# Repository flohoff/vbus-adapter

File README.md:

This repository contains a Vissmann VBUS Adapter KiCad 9 Project.

It uses a Wemos S2 Mini as the ESP32 Interface and offers a
CAN Bus for e.g. Vissmann Vitocal and a VBUS Interface for
connecting to a Vitrotrans a relabeled Resol.

It allows for connecting additional Sensors like DHT22 or DS1820

Currently the project is untested.

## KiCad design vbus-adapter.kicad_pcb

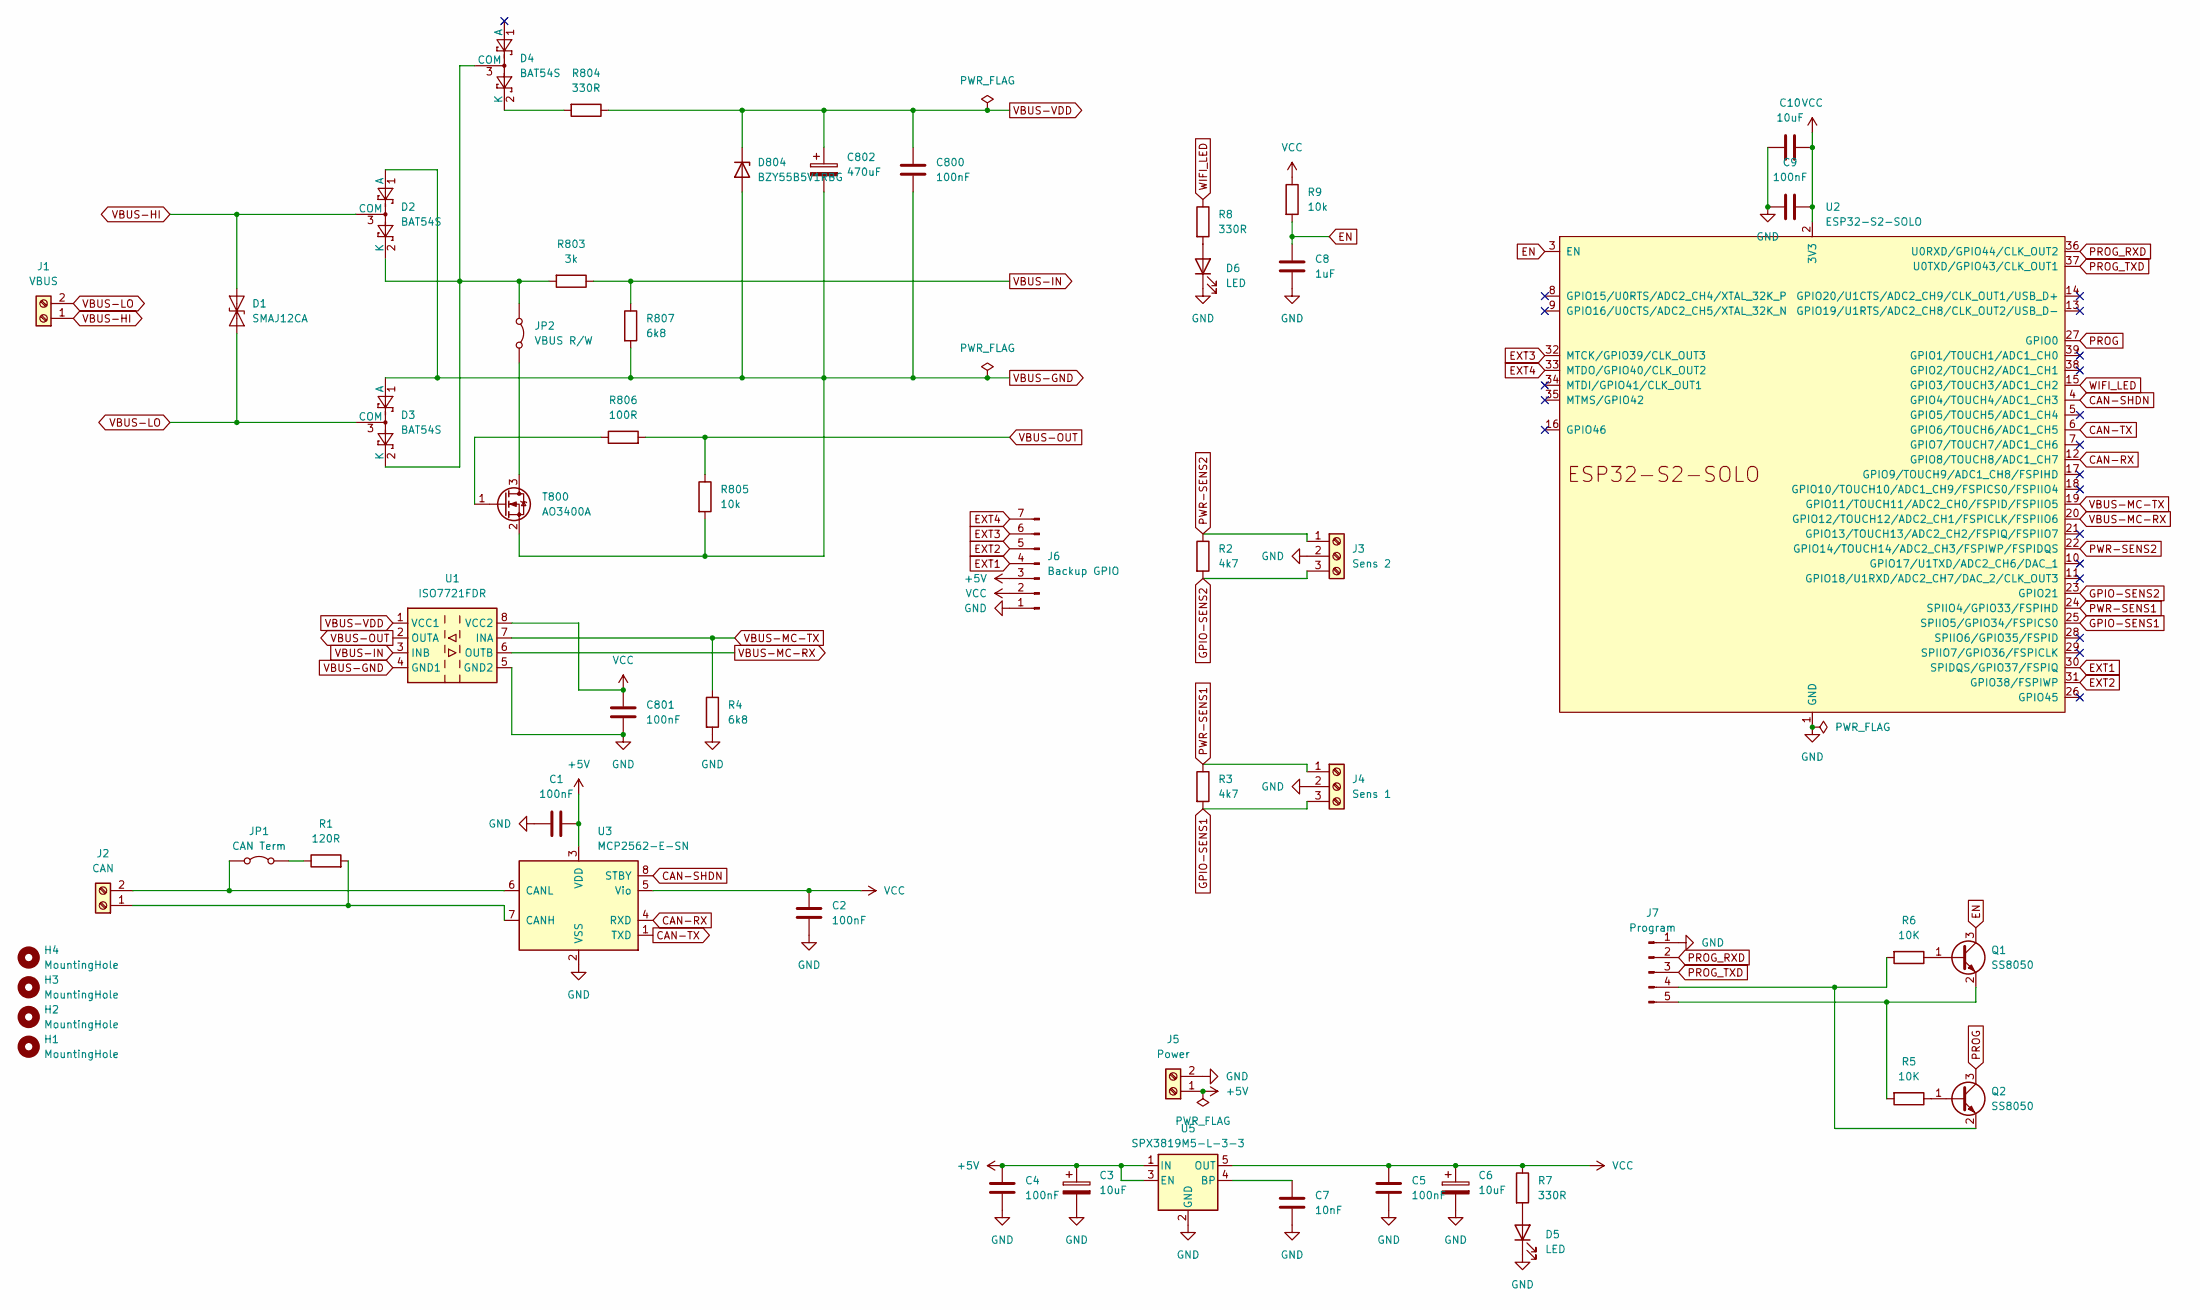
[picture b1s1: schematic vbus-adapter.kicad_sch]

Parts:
C1, C2, C4, C5, C800, C801: 100nF; C_0805_2012Metric_Pad1.18x1.45mm_HandSolder
C3, C6: 10uF; C_0805_2012Metric_Pad1.18x1.45mm_HandSolder
C7: 10nF; C_0805_2012Metric_Pad1.18x1.45mm_HandSolder
C8: 1uF; C_0805_2012Metric
C9: 100nF; C_0805_2012Metric
C10: 10uF; C_0805_2012Metric
C802: 470uF; CP_Elec_8x10
D1: SMAJ12CA; D_SMA
D2, D3, D4: BAT54S; SOT-23
D5, D6: LED; LED_0805_2012Metric_Pad1.15x1.40mm_HandSolder
D804: BZY55B5V1RBG; D_0805_2012Metric
H1, H2, H3, H4: MountingHole; MountingHole_3.2mm_M3_DIN965_Pad
J1: VBUS; TerminalBlock_Phoenix_MPT-0,5-2-2.54_1x02_P2.54mm_Horizontal
J2: CAN; TerminalBlock_Phoenix_MPT-0,5-2-2.54_1x02_P2.54mm_Horizontal
J3: Sens 2; TerminalBlock_Phoenix_MPT-0,5-3-2.54_1x03_P2.54mm_Horizontal
J4: Sens 1; TerminalBlock_Phoenix_MPT-0,5-3-2.54_1x03_P2.54mm_Horizontal
J5: Power; TerminalBlock_Phoenix_MPT-0,5-2-2.54_1x02_P2.54mm_Horizontal
J6: Backup GPIO; PinHeader_1x07_P2.54mm_Vertical
J7: Program; PinHeader_1x05_P2.54mm_Vertical
JP1: CAN Term; PinHeader_1x02_P2.54mm_Vertical
JP2: VBUS R/W; PinHeader_1x02_P2.54mm_Vertical
Q1, Q2: SS8050; SOT-23
R1: 120R; R_0805_2012Metric_Pad1.20x1.40mm_HandSolder
R2, R3: 4k7; R_0805_2012Metric_Pad1.20x1.40mm_HandSolder
R4, R807: 6k8; R_0805_2012Metric_Pad1.20x1.40mm_HandSolder
R5, R6: 10K; R_0805_2012Metric_Pad1.20x1.40mm_HandSolder
R7, R8, R804: 330R; R_0805_2012Metric_Pad1.20x1.40mm_HandSolder
R9: 10k; R_0805_2012Metric
R803: 3k; R_0805_2012Metric_Pad1.20x1.40mm_HandSolder
R805: 10k; R_0805_2012Metric_Pad1.20x1.40mm_HandSolder
R806: 100R; R_0805_2012Metric_Pad1.20x1.40mm_HandSolder
T800: AO3400A; SOT-23
U1: ISO7721FDR; SOIC-8_3.9x4.9mm_P1.27mm
U2: ESP32-S2-SOLO
U3: MCP2562-E-SN; SOIC-8_3.9x4.9mm_P1.27mm
U5: SPX3819M5-L-3-3; SOT-23-5

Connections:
+5V: C1.1, C3.1, C4.1, J5.1, J6.3, U3.3 (VDD), U5.1 (IN), U5.3 (EN)
CAN-RX: U2.12 (GPIO8/TOUCH8/ADC1_CH7), U3.4 (RXD)
CAN-SHDN: U2.4 (GPIO4/TOUCH4/ADC1_CH3), U3.8 (STBY)
CAN-TX: U2.6 (GPIO6/TOUCH6/ADC1_CH5), U3.1 (TXD)
EN: C8.1, Q1.3 (C), R9.2, U2.3 (EN)
EXT1: J6.4, U2.30 (SPIDQS/GPIO37/FSPIQ)
EXT2: J6.5, U2.31 (GPIO38/FSPIWP)
EXT3: J6.6, U2.32 (MTCK/GPIO39/CLK_OUT3)
EXT4: J6.7, U2.33 (MTDO/GPIO40/CLK_OUT2)
GND: C1.2, C2.2, C3.2, C4.2, C5.2, C6.2, C7.2, C8.2, C9.1, C10.1, C801.2, D5.1 (K), D6.1 (K), J3.2, J4.2, J5.2, J6.1, J7.1, R4.2, U1.5 (GND2), U2.1 (GND), U2.40 (GND), U2.41 (GND), U3.2 (VSS), U5.2 (GND)
GPIO-SENS1: J4.3, R3.2, U2.25 (SPIIO5/GPIO34/FSPICS0)
GPIO-SENS2: J3.3, R2.2, U2.23 (GPIO21)
unnamed: D2.2 (K), D3.2 (K), D4.3 (COM), JP2.1 (A), R803.2
unnamed: D4.2 (K), R804.2
unnamed: D5.2 (A), R7.2
unnamed: D6.2 (A), R8.2
unnamed: J2.1, R1.2, U3.7 (CANH)
unnamed: J2.2, JP1.1 (A), U3.6 (CANL)
unnamed: J7.4, Q2.2 (E), R6.2
unnamed: J7.5, Q1.2 (E), R5.2
unnamed: JP1.2 (B), R1.1
unnamed: JP2.2 (B), T800.3 (D)
unnamed: Q1.1 (B), R6.1
unnamed: Q2.1 (B), R5.1
unnamed: R806.1, T800.1 (G)
unnamed: C7.1, U5.4 (BP)
PROG: Q2.3 (C), U2.27 (GPIO0)
PROG_RXD: J7.2, U2.36 (U0RXD/GPIO44/CLK_OUT2)
PROG_TXD: J7.3, U2.37 (U0TXD/GPIO43/CLK_OUT1)
PWR-SENS1: J4.1, R3.1, U2.24 (SPIIO4/GPIO33/FSPIHD)
PWR-SENS2: J3.1, R2.1, U2.22 (GPIO14/TOUCH14/ADC2_CH3/FSPIWP/FSPIDQS)
VBUS-GND: C800.2, C802.2, D2.1 (A), D3.1 (A), D804.2 (A), R805.2, R807.2, T800.2 (S), U1.4 (GND1)
VBUS-HI: D1.1 (A1), D2.3 (COM), J1.1
VBUS-IN: R803.1, R807.1, U1.3 (INB)
VBUS-LO: D1.2 (A2), D3.3 (COM), J1.2
VBUS-MC-RX: U1.6 (OUTB), U2.20 (GPIO12/TOUCH12/ADC2_CH1/FSPICLK/FSPIIO6)
VBUS-MC-TX: R4.1, U1.7 (INA), U2.19 (GPIO11/TOUCH11/ADC2_CH0/FSPID/FSPIIO5)
VBUS-OUT: R805.1, R806.2, U1.2 (OUTA)
VBUS-VDD: C800.1, C802.1, D804.1 (K), R804.1, U1.1 (VCC1)
VCC: C2.1, C5.1, C6.1, C9.2, C10.2, C801.1, J6.2, R7.1, R9.1, U1.8 (VCC2), U2.2 (3V3), U3.5 (Vio), U5.5 (OUT)
WIFI_LED: R8.1, U2.15 (GPIO3/TOUCH3/ADC1_CH2)

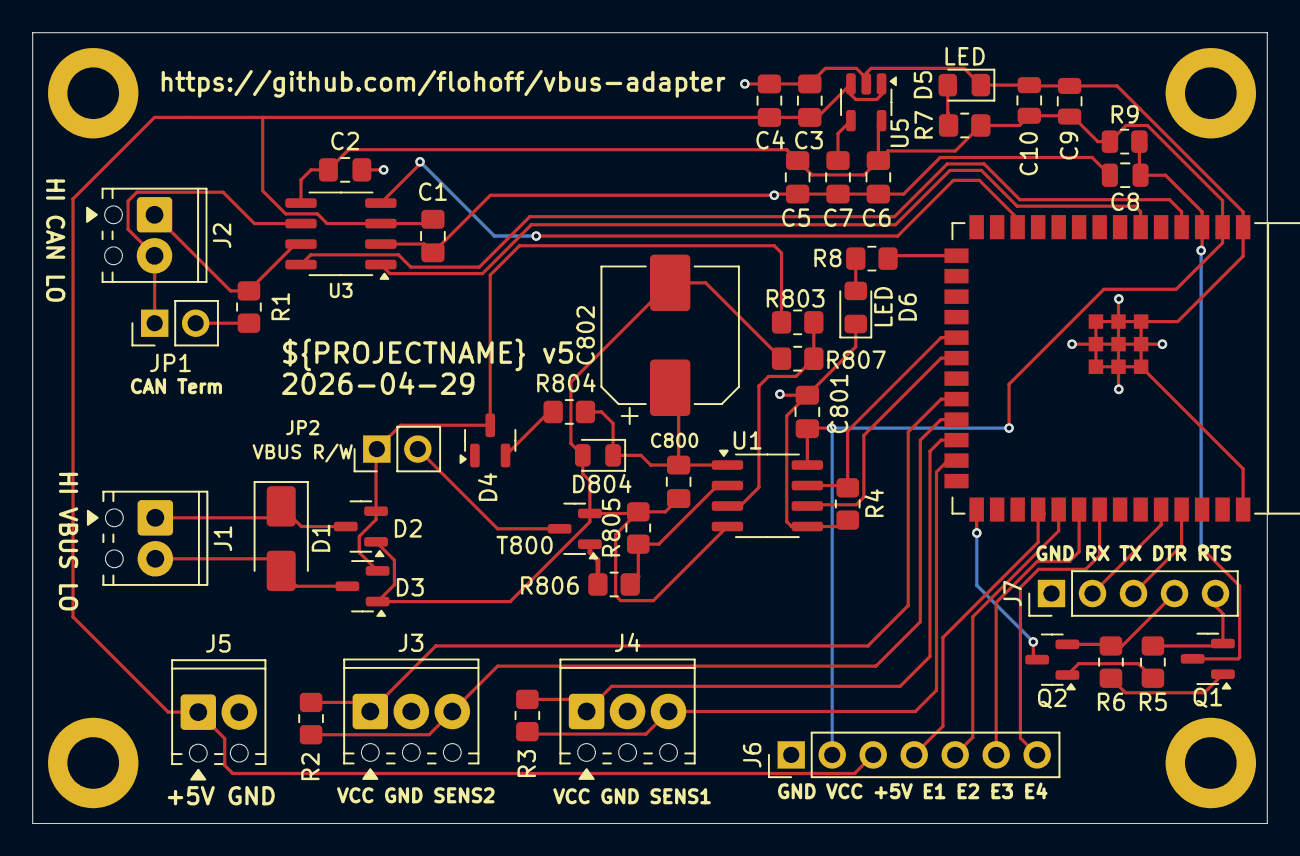
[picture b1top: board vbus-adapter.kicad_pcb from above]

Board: 2 copper layers, 76.5 x 49.0 mm, 54 parts (0 on the bottom side), 41 nets.

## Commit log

2026-01-12 First version
2026-01-12 Add boardview
2026-01-12 Make boardview really a jpeg
2026-01-12 Mention Resol
2026-03-13 Fix footprint for C802
2026-04-06 Fixed power connection for U3 (MCP2562) Changed Z-Diode to BZY55B5V1RBG with 0805 pinout Added 10k pullup to ESP32 EN pin Added 1uF capacitor to ESP32 EN pin Added 100nF and 10uF capacitor to ESP32 V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
2026-04-29 Version 4
2026-04-29 Version 5
    - Reposition connectors for Programming
    - Add +5V to Sensor Connector
    - Make VCC on SENS connector from GPIO
2026-04-29 Small fixes
    - Label placement
    - Remove redundant PWR_FLAG
2026-04-29 Fix programming adapter Labeling
